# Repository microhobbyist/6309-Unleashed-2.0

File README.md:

# 6309 Unleashed 2.0
 New and upgraded 6309 build - with NITROS-9 in mind!

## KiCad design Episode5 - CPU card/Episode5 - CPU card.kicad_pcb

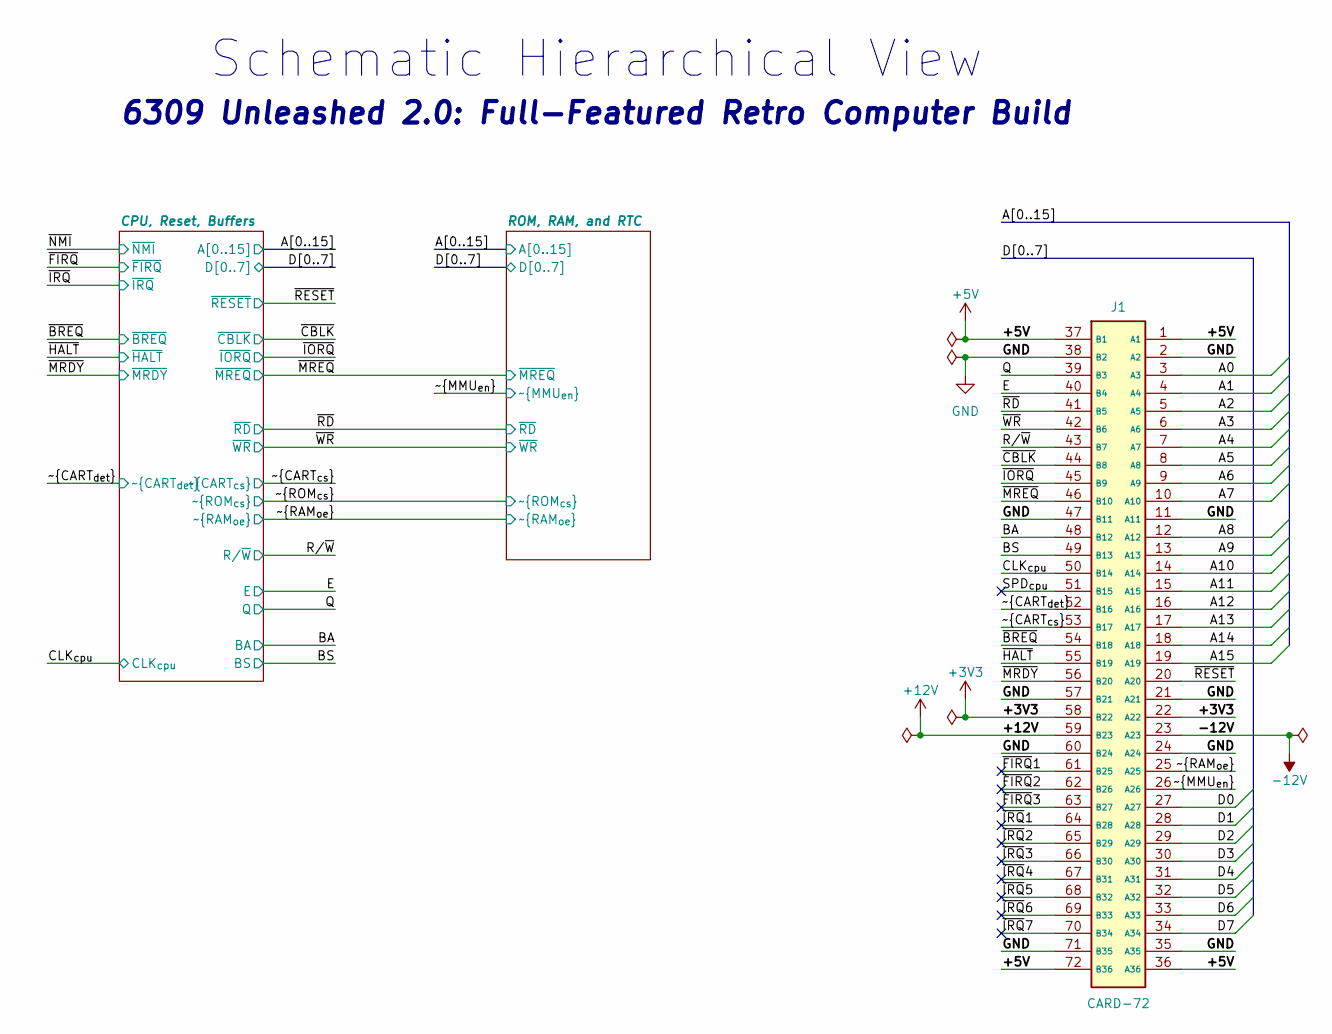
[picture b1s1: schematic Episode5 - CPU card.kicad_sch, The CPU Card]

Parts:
J1: CARD-72; 72-pin Card Edge PCB; Mouser Part Number 571-5530843-8

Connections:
+3V3: J1.22 (A22), J1.58 (B22)
+5V: J1.1 (A1), J1.36 (A36), J1.37 (B1), J1.72 (B36); also elsewhere on the board
+12V: J1.59 (B23)
-12V: J1.23 (A23)
/A0: J1.3 (A3); also elsewhere on the board
/A1: J1.4 (A4); also elsewhere on the board
/A2: J1.5 (A5); also elsewhere on the board
/A3: J1.6 (A6); also elsewhere on the board
/A4: J1.7 (A7); also elsewhere on the board
/A5: J1.8 (A8); also elsewhere on the board
/A6: J1.9 (A9); also elsewhere on the board
/A7: J1.10 (A10); also elsewhere on the board
/A8: J1.12 (A12); also elsewhere on the board
/A9: J1.13 (A13); also elsewhere on the board
/A10: J1.14 (A14); also elsewhere on the board
/A11: J1.15 (A15); also elsewhere on the board
/A12: J1.16 (A16); also elsewhere on the board
/A13: J1.17 (A17); also elsewhere on the board
/A14: J1.18 (A18); also elsewhere on the board
/A15: J1.19 (A19); also elsewhere on the board
/BA: J1.48 (B12); also elsewhere on the board
/BS: J1.49 (B13); also elsewhere on the board
/CLK_{cpu}: J1.50 (B14); also elsewhere on the board
/D0: J1.27 (A27); also elsewhere on the board
/D1: J1.28 (A28); also elsewhere on the board
/D2: J1.29 (A29); also elsewhere on the board
/D3: J1.30 (A30); also elsewhere on the board
/D4: J1.31 (A31); also elsewhere on the board
/D5: J1.32 (A32); also elsewhere on the board
/D6: J1.33 (A33); also elsewhere on the board
/D7: J1.34 (A34); also elsewhere on the board
/E: J1.40 (B4); also elsewhere on the board
/Q: J1.39 (B3); also elsewhere on the board
/R/~W: J1.43 (B7); also elsewhere on the board
/SPD_{cpu}: J1.51 (B15)
/~BREQ: J1.54 (B18); also elsewhere on the board
/~CART_{cs}: J1.53 (B17); also elsewhere on the board
/~CART_{det}: J1.52 (B16); also elsewhere on the board
/~CBLK: J1.44 (B8); also elsewhere on the board
/~FIRQ1: J1.61 (B25)
/~FIRQ2: J1.62 (B26)
/~FIRQ3: J1.63 (B27)
/~HALT: J1.55 (B19); also elsewhere on the board
/~IORQ: J1.45 (B9); also elsewhere on the board
/~IRQ1: J1.64 (B28)
/~IRQ2: J1.65 (B29)
/~IRQ3: J1.66 (B30)
/~IRQ4: J1.67 (B31)
/~IRQ5: J1.68 (B32)
/~IRQ6: J1.69 (B33)
/~IRQ7: J1.70 (B34)
/~MMU_{en}: J1.26 (A26); also elsewhere on the board
/~MRDY: J1.56 (B20); also elsewhere on the board
/~MREQ: J1.46 (B10); also elsewhere on the board
/~RAM_{oe}: J1.25 (A25); also elsewhere on the board
/~RD: J1.41 (B5); also elsewhere on the board
/~RESET: J1.20 (A20); also elsewhere on the board
/~WR: J1.42 (B6); also elsewhere on the board
GND: J1.2 (A2), J1.11 (A11), J1.21 (A21), J1.24 (A24), J1.35 (A35), J1.38 (B2), J1.47 (B11), J1.57 (B21), J1.60 (B24), J1.71 (B35); also elsewhere on the board

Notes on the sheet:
6309 Unleashed 2.0: Full-Featured Retro Computer Build
Schematic Hierarchical View

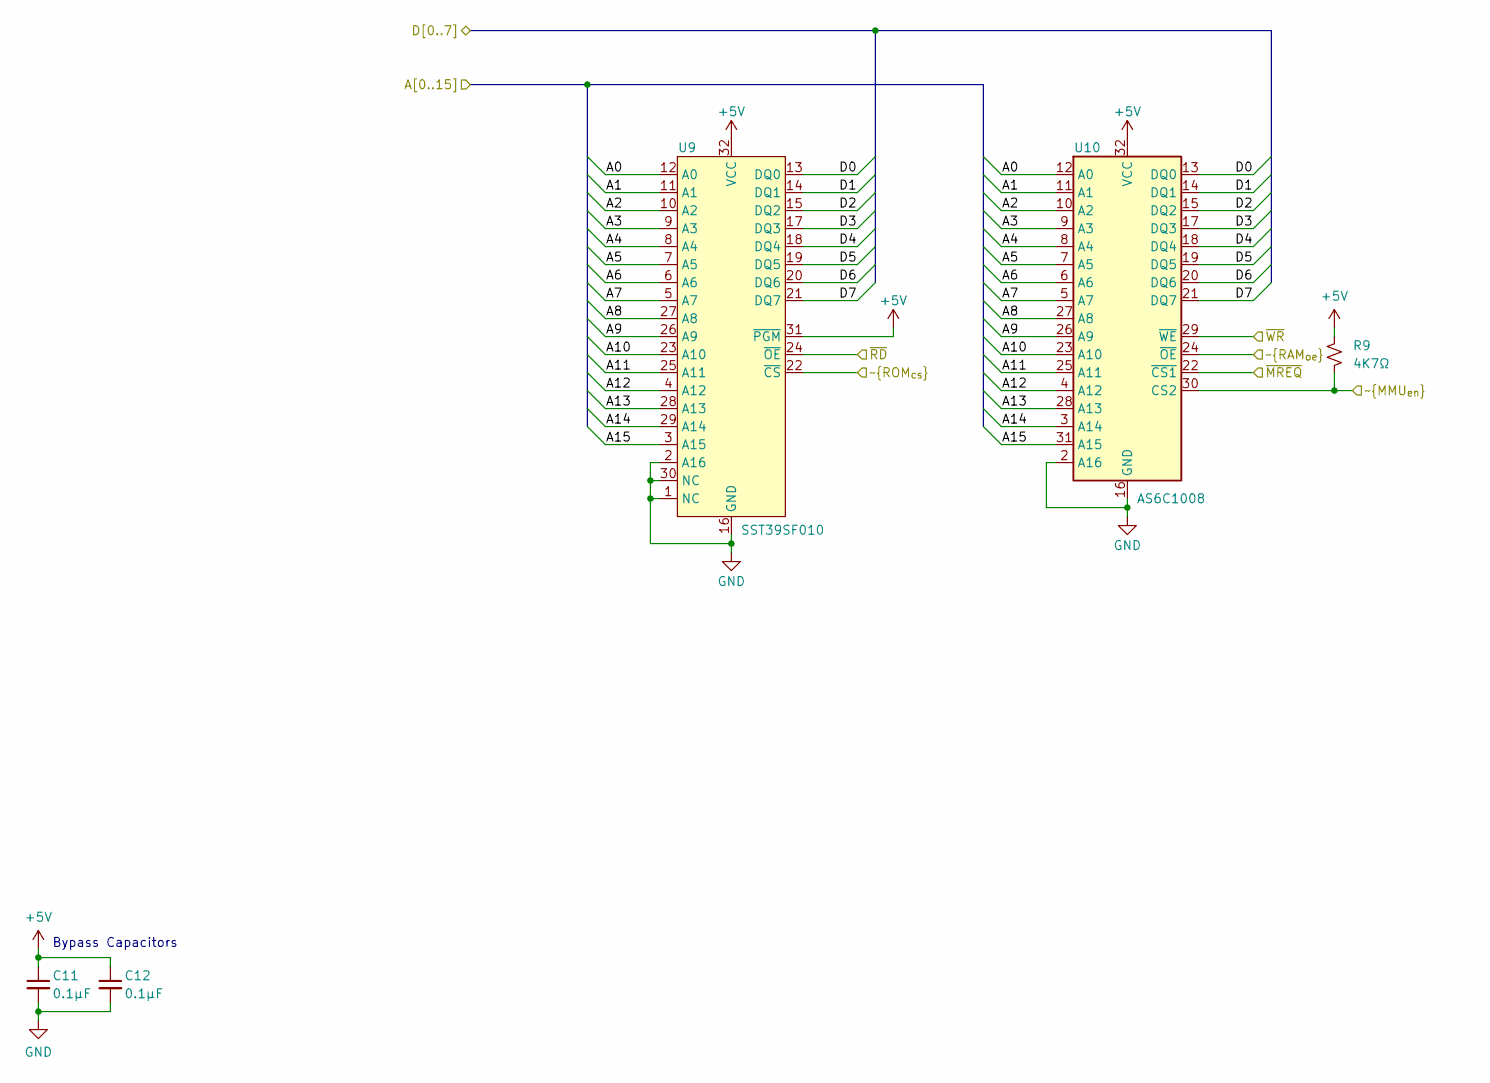
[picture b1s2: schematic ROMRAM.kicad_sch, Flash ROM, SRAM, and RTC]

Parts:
C11, C12: 0.1µF; C_Disc_D3.0mm_W1.6mm_P2.50mm
R9: 4K7Ω; R_Axial_DIN0207_L6.3mm_D2.5mm_P10.16mm_Horizontal
U9: SST39SF010; DIP_Socket-32_W11.9mm_W12.7mm_W15.24mm_W17.78mm_W18.5mm_3M_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
U10: AS6C1008; DIP-32_W15.24mm_Socket

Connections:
+5V: C11.1, C12.1, R9.2, U9.31 (~PGM), U9.32 (VCC), U10.32 (VCC); also elsewhere on the board
/A0: U9.12 (A0), U10.12 (A0); also elsewhere on the board
/A1: U9.11 (A1), U10.11 (A1); also elsewhere on the board
/A2: U9.10 (A2), U10.10 (A2); also elsewhere on the board
/A3: U9.9 (A3), U10.9 (A3); also elsewhere on the board
/A4: U9.8 (A4), U10.8 (A4); also elsewhere on the board
/A5: U9.7 (A5), U10.7 (A5); also elsewhere on the board
/A6: U9.6 (A6), U10.6 (A6); also elsewhere on the board
/A7: U9.5 (A7), U10.5 (A7); also elsewhere on the board
/A8: U9.27 (A8), U10.27 (A8); also elsewhere on the board
/A9: U9.26 (A9), U10.26 (A9); also elsewhere on the board
/A10: U9.23 (A10), U10.23 (A10); also elsewhere on the board
/A11: U9.25 (A11), U10.25 (A11); also elsewhere on the board
/A12: U9.4 (A12), U10.4 (A12); also elsewhere on the board
/A13: U9.28 (A13), U10.28 (A13); also elsewhere on the board
/A14: U9.29 (A14), U10.3 (A14); also elsewhere on the board
/A15: U9.3 (A15), U10.31 (A15); also elsewhere on the board
/D0: U9.13 (DQ0), U10.13 (DQ0); also elsewhere on the board
/D1: U9.14 (DQ1), U10.14 (DQ1); also elsewhere on the board
/D2: U9.15 (DQ2), U10.15 (DQ2); also elsewhere on the board
/D3: U9.17 (DQ3), U10.17 (DQ3); also elsewhere on the board
/D4: U9.18 (DQ4), U10.18 (DQ4); also elsewhere on the board
/D5: U9.19 (DQ5), U10.19 (DQ5); also elsewhere on the board
/D6: U9.20 (DQ6), U10.20 (DQ6); also elsewhere on the board
/D7: U9.21 (DQ7), U10.21 (DQ7); also elsewhere on the board
/~MMU_{en}: R9.1, U10.30 (CS2); also elsewhere on the board
/~MREQ: U10.22 (~CS1); also elsewhere on the board
/~RAM_{oe}: U10.24 (~OE); also elsewhere on the board
/~RD: U9.24 (~OE); also elsewhere on the board
/~ROM_{cs}: U9.22 (~CS); also elsewhere on the board
/~WR: U10.29 (~WE); also elsewhere on the board
GND: C11.2, C12.2, U9.1 (NC), U9.2 (A16), U9.16 (GND), U9.30 (NC), U10.2 (A16), U10.16 (GND); also elsewhere on the board

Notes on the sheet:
Bypass Capacitors

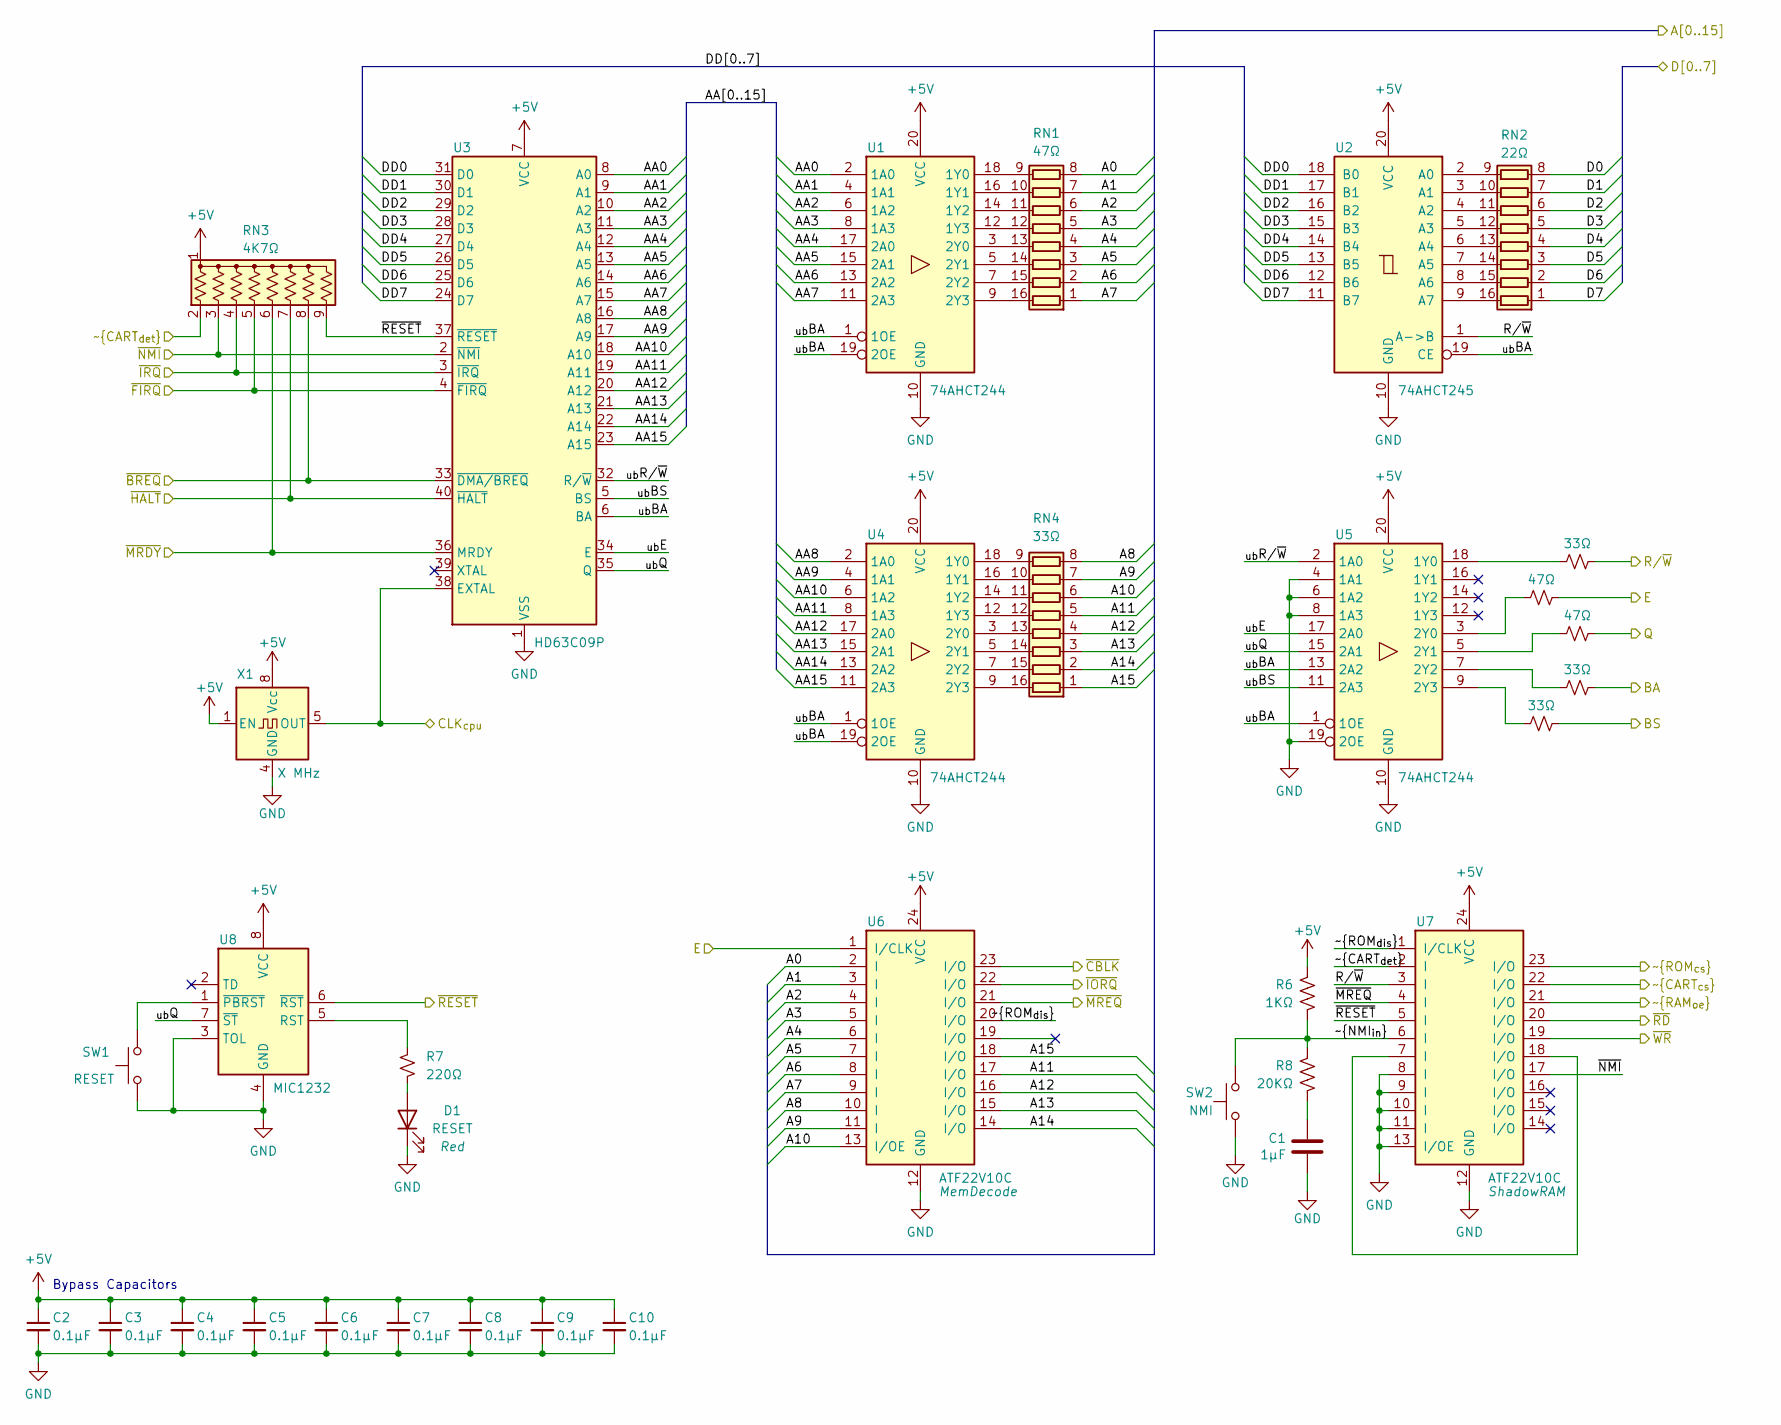
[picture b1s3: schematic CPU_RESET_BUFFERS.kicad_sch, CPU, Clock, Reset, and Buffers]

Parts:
C1: 1µF; C_Disc_D3.0mm_W1.6mm_P2.50mm
C2, C3, C4, C5, C6, C7, C8, C9, C10: 0.1µF; C_Disc_D3.0mm_W1.6mm_P2.50mm
D1: RESET; LED_D5.0mm
R1, R4, R5: 33Ω; R_Axial_DIN0207_L6.3mm_D2.5mm_P10.16mm_Horizontal
R2, R3: 47Ω; R_Axial_DIN0207_L6.3mm_D2.5mm_P10.16mm_Horizontal
R6: 1KΩ; R_Axial_DIN0207_L6.3mm_D2.5mm_P10.16mm_Horizontal
R7: 220Ω; R_Axial_DIN0207_L6.3mm_D2.5mm_P10.16mm_Horizontal
R8: 20KΩ; R_Axial_DIN0207_L6.3mm_D2.5mm_P10.16mm_Horizontal
RN1: 47Ω; DIP-16_W7.62mm_Socket
RN2: 22Ω; DIP-16_W7.62mm_Socket
RN3: 4K7Ω; R_Array_SIP9
RN4: 33Ω; DIP-16_W7.62mm_Socket
SW1: RESET; SW_Tactile_SKHH_Angled
SW2: NMI; SW_Tactile_SKHH_Angled
U1, U4, U5: 74AHCT244; DIP-20_W7.62mm_Socket
U2: 74AHCT245; DIP-20_W7.62mm_Socket
U3: HD63C09P; DIP-40_W15.24mm_Socket
U6, U7: ATF22V10C; DIP-24_W7.62mm_Socket
U8: MIC1232; DIP-8_W7.62mm_Socket
X1: X MHz; Oscillator_DIP-8

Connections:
+5V: C2.1, C3.1, C4.1, C5.1, C6.1, C7.1, C8.1, C9.1, C10.1, R6.1, RN3.1 (common), U1.20 (VCC), U2.20 (VCC), U3.7 (VCC), U4.20 (VCC), U5.20 (VCC), U6.24 (VCC), U7.24 (VCC), U8.8 (VCC), X1.1 (EN), X1.8 (Vcc); also elsewhere on the board
/A0: RN1.8 (R8.1), U6.2 (I); also elsewhere on the board
/A1: RN1.7 (R7.1), U6.3 (I); also elsewhere on the board
/A2: RN1.6 (R6.1), U6.4 (I); also elsewhere on the board
/A3: RN1.5 (R5.1), U6.5 (I); also elsewhere on the board
/A4: RN1.4 (R4.1), U6.6 (I); also elsewhere on the board
/A5: RN1.3 (R3.1), U6.7 (I); also elsewhere on the board
/A6: RN1.2 (R2.1), U6.8 (I); also elsewhere on the board
/A7: RN1.1 (R1.1), U6.9 (I); also elsewhere on the board
/A8: RN4.8 (R8.1), U6.10 (I); also elsewhere on the board
/A9: RN4.7 (R7.1), U6.11 (I); also elsewhere on the board
/A10: RN4.6 (R6.1), U6.13 (I/OE); also elsewhere on the board
/A11: RN4.5 (R5.1), U6.17 (I/O); also elsewhere on the board
/A12: RN4.4 (R4.1), U6.16 (I/O); also elsewhere on the board
/A13: RN4.3 (R3.1), U6.15 (I/O); also elsewhere on the board
/A14: RN4.2 (R2.1), U6.14 (I/O); also elsewhere on the board
/A15: RN4.1 (R1.1), U6.18 (I/O); also elsewhere on the board
/BA: R4.2; also elsewhere on the board
/BS: R5.2; also elsewhere on the board
/CLK_{cpu}: U3.38 (EXTAL), X1.5 (OUT); also elsewhere on the board
/CPU, Reset, Buffers/AA0: U1.2 (1A0), U3.8 (A0)
/CPU, Reset, Buffers/AA1: U1.4 (1A1), U3.9 (A1)
/CPU, Reset, Buffers/AA2: U1.6 (1A2), U3.10 (A2)
/CPU, Reset, Buffers/AA3: U1.8 (1A3), U3.11 (A3)
/CPU, Reset, Buffers/AA4: U1.17 (2A0), U3.12 (A4)
/CPU, Reset, Buffers/AA5: U1.15 (2A1), U3.13 (A5)
/CPU, Reset, Buffers/AA6: U1.13 (2A2), U3.14 (A6)
/CPU, Reset, Buffers/AA7: U1.11 (2A3), U3.15 (A7)
/CPU, Reset, Buffers/AA8: U3.16 (A8), U4.2 (1A0)
/CPU, Reset, Buffers/AA9: U3.17 (A9), U4.4 (1A1)
/CPU, Reset, Buffers/AA10: U3.18 (A10), U4.6 (1A2)
/CPU, Reset, Buffers/AA11: U3.19 (A11), U4.8 (1A3)
/CPU, Reset, Buffers/AA12: U3.20 (A12), U4.17 (2A0)
/CPU, Reset, Buffers/AA13: U3.21 (A13), U4.15 (2A1)
/CPU, Reset, Buffers/AA14: U3.22 (A14), U4.13 (2A2)
/CPU, Reset, Buffers/AA15: U3.23 (A15), U4.11 (2A3)
/CPU, Reset, Buffers/DD0: U2.18 (B0), U3.31 (D0)
/CPU, Reset, Buffers/DD1: U2.17 (B1), U3.30 (D1)
/CPU, Reset, Buffers/DD2: U2.16 (B2), U3.29 (D2)
/CPU, Reset, Buffers/DD3: U2.15 (B3), U3.28 (D3)
/CPU, Reset, Buffers/DD4: U2.14 (B4), U3.27 (D4)
/CPU, Reset, Buffers/DD5: U2.13 (B5), U3.26 (D5)
/CPU, Reset, Buffers/DD6: U2.12 (B6), U3.25 (D6)
/CPU, Reset, Buffers/DD7: U2.11 (B7), U3.24 (D7)
/CPU, Reset, Buffers/_{ub}BA: U1.1 (1OE), U1.19 (2OE), U2.19 (CE), U3.6 (BA), U4.1 (1OE), U4.19 (2OE), U5.1 (1OE), U5.13 (2A2)
/CPU, Reset, Buffers/_{ub}BS: U3.5 (BS), U5.11 (2A3)
/CPU, Reset, Buffers/_{ub}E: U3.34 (E), U5.17 (2A0)
/CPU, Reset, Buffers/_{ub}Q: U3.35 (Q), U5.15 (2A1), U8.7 (~ST)
/CPU, Reset, Buffers/_{ub}R/~W: U3.32 (R/~W), U5.2 (1A0)
/CPU, Reset, Buffers/~NMI_{in}: R6.2, R8.1, SW2.2, U7.6 (I)
/CPU, Reset, Buffers/~ROM_{dis}: U6.20 (I/O), U7.1 (I/CLK)
/D0: RN2.8 (R8.1); also elsewhere on the board
/D1: RN2.7 (R7.1); also elsewhere on the board
/D2: RN2.6 (R6.1); also elsewhere on the board
/D3: RN2.5 (R5.1); also elsewhere on the board
/D4: RN2.4 (R4.1); also elsewhere on the board
/D5: RN2.3 (R3.1); also elsewhere on the board
/D6: RN2.2 (R2.1); also elsewhere on the board
/D7: RN2.1 (R1.1); also elsewhere on the board
/E: R2.2, U6.1 (I/CLK); also elsewhere on the board
/Q: R3.2; also elsewhere on the board
/R/~W: R1.2, U2.1 (A->B), U7.3 (I); also elsewhere on the board
/~BREQ: RN3.8 (R7), U3.33 (~DMA/BREQ); also elsewhere on the board
/~CART_{cs}: U7.22 (I/O); also elsewhere on the board
/~CART_{det}: RN3.2 (R1), U7.2 (I); also elsewhere on the board
/~CBLK: U6.23 (I/O); also elsewhere on the board
/~FIRQ: RN3.5 (R4), U3.4 (~FIRQ)
/~HALT: RN3.7 (R6), U3.40 (~HALT); also elsewhere on the board
/~IORQ: U6.22 (I/O); also elsewhere on the board
/~IRQ: RN3.4 (R3), U3.3 (~IRQ)
/~MRDY: RN3.6 (R5), U3.36 (MRDY); also elsewhere on the board
/~MREQ: U6.21 (I/O), U7.4 (I); also elsewhere on the board
/~NMI: RN3.3 (R2), U3.2 (~NMI), U7.17 (I/O)
/~RAM_{oe}: U7.21 (I/O); also elsewhere on the board
/~RD: U7.20 (I/O); also elsewhere on the board
/~RESET: RN3.9 (R8), U3.37 (~RESET), U7.5 (I), U8.6 (~RST); also elsewhere on the board
/~ROM_{cs}: U7.23 (I/O); also elsewhere on the board
/~WR: U7.19 (I/O); also elsewhere on the board
GND: C1.2, C2.2, C3.2, C4.2, C5.2, C6.2, C7.2, C8.2, C9.2, C10.2, D1.1 (K), SW1.1, SW2.1, U1.10 (GND), U2.10 (GND), U3.1 (VSS), U4.10 (GND), U5.4 (1A1), U5.6 (1A2), U5.8 (1A3), U5.10 (GND), U5.19 (2OE), U6.12 (GND), U7.8 (I), U7.9 (I), U7.10 (I), U7.11 (I), U7.12 (GND), U7.13 (I/OE), U8.3 (TOL), U8.4 (GND), X1.4 (GND); also elsewhere on the board
unnamed: C1.1, R8.2
unnamed: D1.2 (A), R7.1
unnamed: RN1.16 (R1.2), U1.9 (2Y3)
unnamed: RN1.15 (R2.2), U1.7 (2Y2)
unnamed: RN1.14 (R3.2), U1.5 (2Y1)
unnamed: RN1.13 (R4.2), U1.3 (2Y0)
unnamed: RN1.12 (R5.2), U1.12 (1Y3)
unnamed: RN1.11 (R6.2), U1.14 (1Y2)
unnamed: RN1.10 (R7.2), U1.16 (1Y1)
unnamed: RN1.9 (R8.2), U1.18 (1Y0)
unnamed: RN2.16 (R1.2), U2.9 (A7)
unnamed: RN2.15 (R2.2), U2.8 (A6)
unnamed: RN2.14 (R3.2), U2.7 (A5)
unnamed: RN2.13 (R4.2), U2.6 (A4)
unnamed: RN2.12 (R5.2), U2.5 (A3)
unnamed: RN2.11 (R6.2), U2.4 (A2)
unnamed: RN2.10 (R7.2), U2.3 (A1)
unnamed: RN2.9 (R8.2), U2.2 (A0)
unnamed: RN4.16 (R1.2), U4.9 (2Y3)
unnamed: RN4.15 (R2.2), U4.7 (2Y2)
unnamed: RN4.14 (R3.2), U4.5 (2Y1)
unnamed: RN4.13 (R4.2), U4.3 (2Y0)
unnamed: RN4.12 (R5.2), U4.12 (1Y3)
unnamed: RN4.11 (R6.2), U4.14 (1Y2)
unnamed: RN4.10 (R7.2), U4.16 (1Y1)
unnamed: RN4.9 (R8.2), U4.18 (1Y0)
unnamed: R1.1, U5.18 (1Y0)
unnamed: R2.1, U5.3 (2Y0)
unnamed: R3.1, U5.5 (2Y1)
unnamed: R4.1, U5.7 (2Y2)
unnamed: R5.1, U5.9 (2Y3)
unnamed: U7.7 (I), U7.18 (I/O)
unnamed: R7.2, U8.5 (RST)
unnamed: SW1.2, U8.1 (~PBRST)

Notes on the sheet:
Bypass Capacitors

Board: 2 copper layers, 40 parts (0 on the bottom side), 115 nets, no tracks yet.
